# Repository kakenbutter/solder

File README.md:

# A 2-Bit Adder - *solder*
A poorly made PCB that is only slightly smarter than a goldfish. Ever wished to know the answer to life, the universe, and everything? Well this certainly can't tell you, but it can tell you what 3 + 3 is! Cool!

## Schematic

## PCB

## Features
- Won't explode/spontaneously combust*!
- Can add 2 numbers up to 3*!
- Turn on and off with potentiometer*!
- "Clean and neat" wiring on PCB*!

**probably*

## BOM
- 1 	Battery holder
- 6 	PNP Transistor
- 15	NPN Transistor
- 18  220k Resistor
- 1 	Potentiometer
- 4 	Push Button
- 4   LED

---

I do not assume any responsibility for any damage caused by using this PCB. 

Made by `@Ethan Zhou` as a part of https://solder.hackclub.com!

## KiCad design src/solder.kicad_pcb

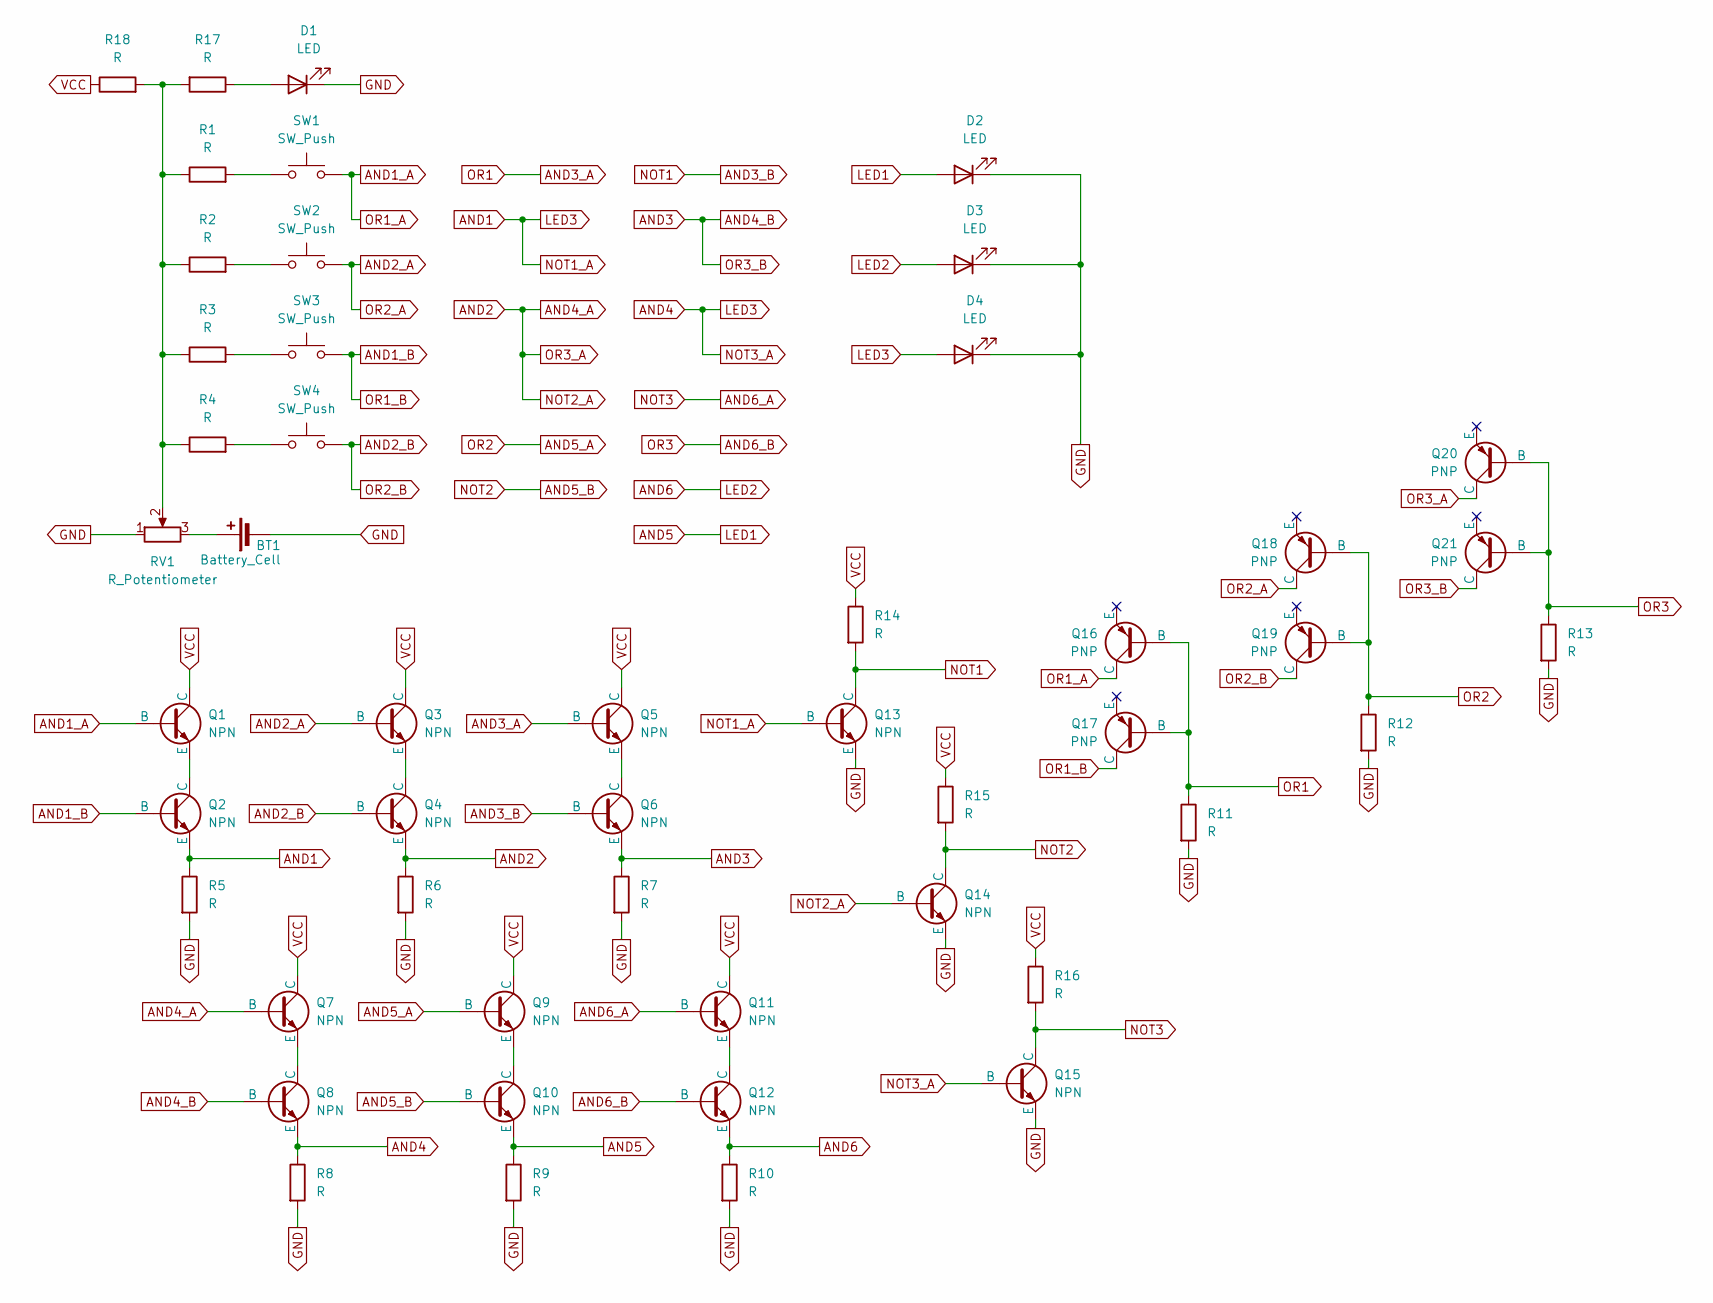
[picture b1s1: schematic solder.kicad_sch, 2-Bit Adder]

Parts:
BT1: Battery_Cell; BatteryHolder_Keystone_3034_1x20mm
D1, D2, D3, D4: LED; LED_D5.0mm
Q1, Q2, Q3, Q4, Q5, Q6, Q7, Q8, Q9, Q10, Q11, Q12, Q13, Q14, Q15: NPN; TO-92L_HandSolder
Q16, Q17, Q18, Q19, Q20, Q21: PNP; TO-92L_HandSolder
R1, R2, R3, R4, R5, R6, R7, R8, R9, R10, R11, R12, R13, R14, R15, R16, R17, R18: R; R_Axial_DIN0207_L6.3mm_D2.5mm_P7.62mm_Horizontal
RV1: R_Potentiometer; Potentiometer_Vishay_T73YP_Vertical
SW1, SW2, SW3, SW4: SW_Push; SW_PUSH_6mm

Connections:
AND1: D4.2 (A), Q2.3 (E), Q8.3 (E), Q13.2 (B), Q15.2 (B), R5.1, R8.1
AND1_A: Q1.2 (B), Q16.1 (C), SW1.2
AND1_B: Q2.2 (B), Q17.1 (C), SW3.2
AND2: Q4.3 (E), Q7.2 (B), Q14.2 (B), Q20.1 (C), R6.1
AND2_A: Q3.2 (B), Q18.1 (C), SW2.2
AND2_B: Q4.2 (B), Q19.1 (C), SW4.2
AND3: Q6.3 (E), Q8.2 (B), Q21.1 (C), R7.1
AND3_A: Q5.2 (B), Q16.2 (B), Q17.2 (B), R11.1
AND3_B: Q6.2 (B), Q13.1 (C), R14.2
AND5: D2.2 (A), Q10.3 (E), R9.1
AND5_A: Q9.2 (B), Q18.2 (B), Q19.2 (B), R12.1
AND5_B: Q10.2 (B), Q14.1 (C), R15.2
AND6: D3.2 (A), Q12.3 (E), R10.1
AND6_A: Q11.2 (B), Q15.1 (C), R16.2
AND6_B: Q12.2 (B), Q20.2 (B), Q21.2 (B), R13.1
GND: BT1.2 (-), D1.1 (K), D2.1 (K), D3.1 (K), D4.1 (K), Q13.3 (E), Q14.3 (E), Q15.3 (E), R5.2, R6.2, R7.2, R8.2, R9.2, R10.2, R11.2, R12.2, R13.2, RV1.1
unnamed: BT1.1 (+), RV1.3
unnamed: D1.2 (A), R17.1
unnamed: Q1.3 (E), Q2.1 (C)
unnamed: Q3.3 (E), Q4.1 (C)
unnamed: Q5.3 (E), Q6.1 (C)
unnamed: Q7.3 (E), Q8.1 (C)
unnamed: Q9.3 (E), Q10.1 (C)
unnamed: Q11.3 (E), Q12.1 (C)
unnamed: R1.1, R2.1, R3.1, R4.1, R17.2, R18.2, RV1.2
unnamed: R1.2, SW1.1
unnamed: R2.2, SW2.1
unnamed: R3.2, SW3.1
unnamed: R4.2, SW4.1
VCC: Q1.1 (C), Q3.1 (C), Q5.1 (C), Q7.1 (C), Q9.1 (C), Q11.1 (C), R14.1, R15.1, R16.1, R18.1

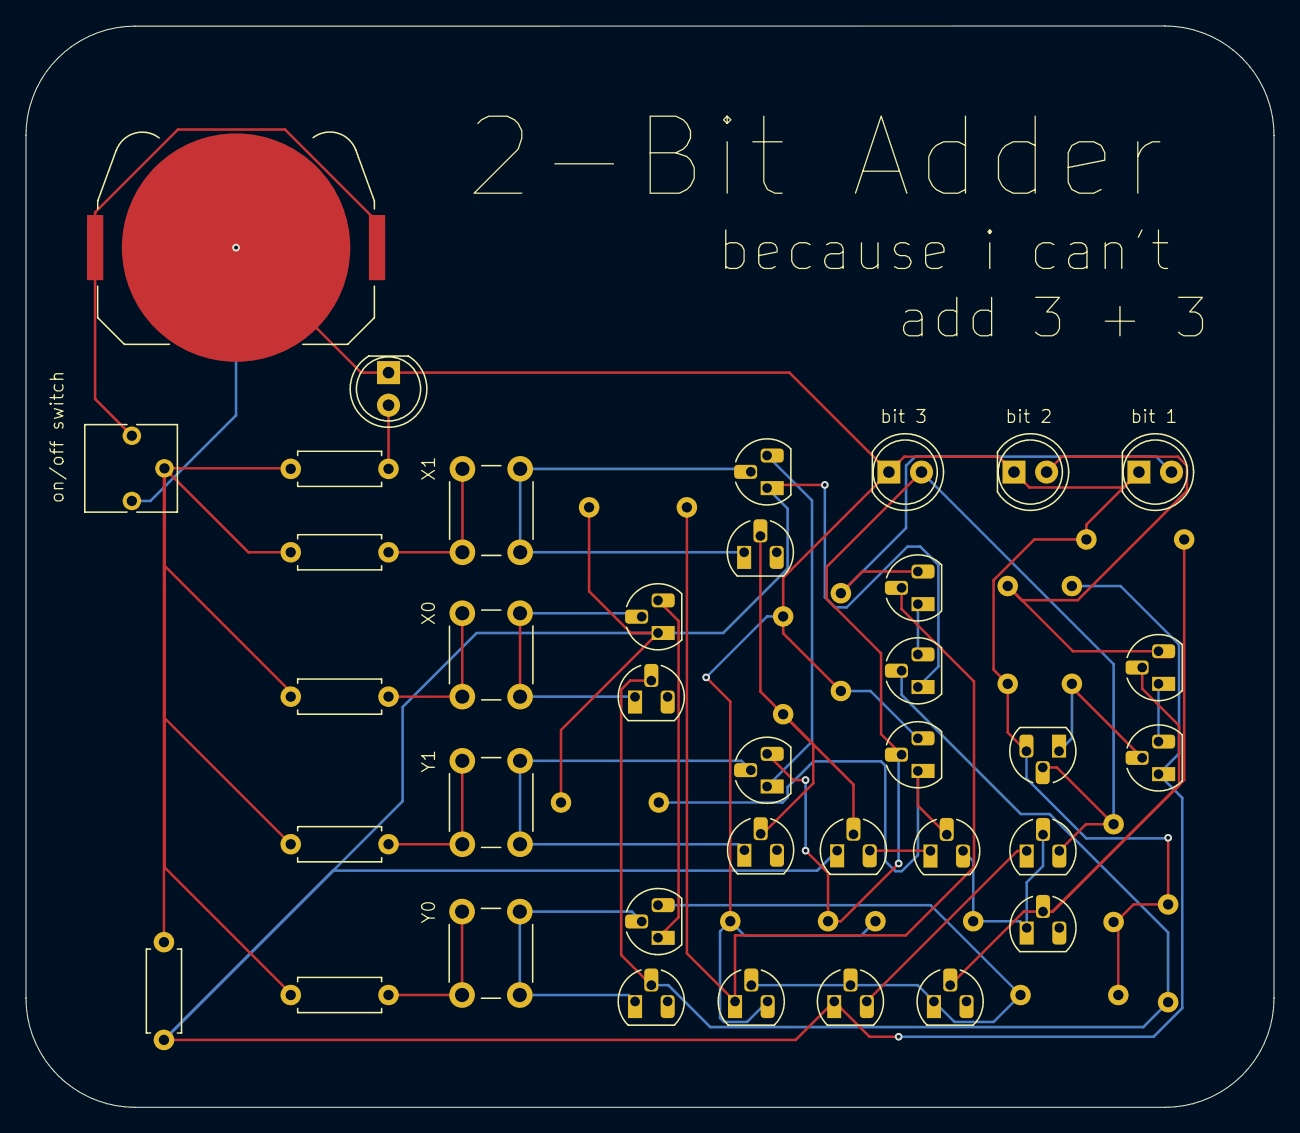
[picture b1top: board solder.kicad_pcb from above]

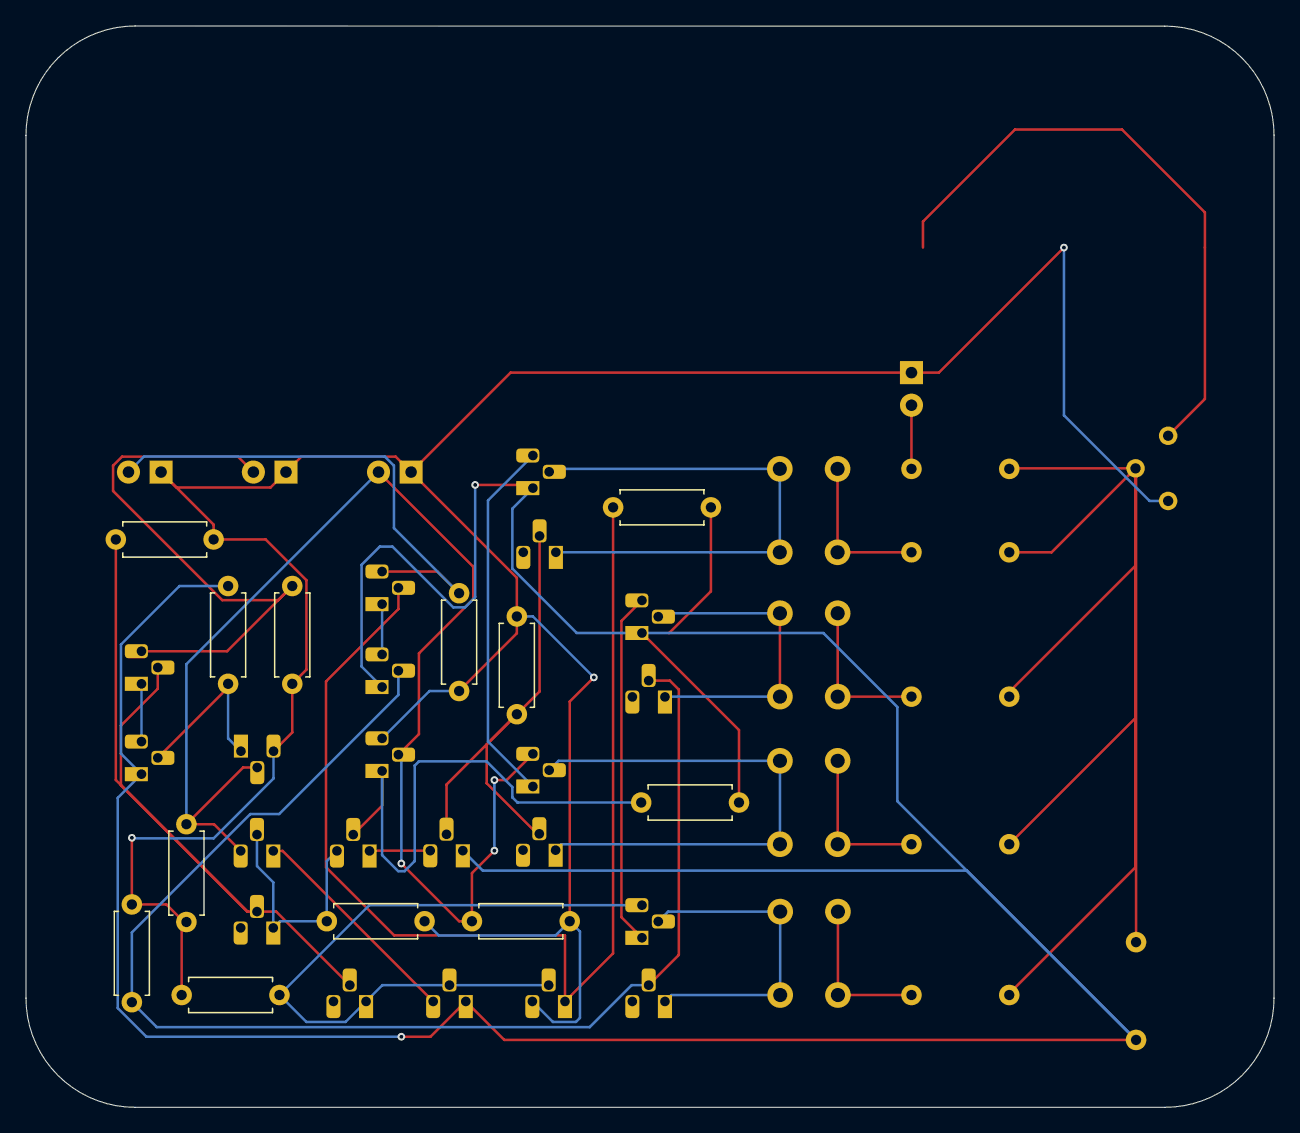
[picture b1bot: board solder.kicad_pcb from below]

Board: 2 copper layers, 97.2 x 84.3 mm, 49 parts (12 on the bottom side), 30 nets.

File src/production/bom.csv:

Designator,Footprint,Quantity,Value,LCSC Part #
BT1,BatteryHolder_Keystone_3034_1x20mm,1,Battery_Cell,
"D1, D2, D3, D4",LED_D5.0mm,4,LED,
"Q1, Q10, Q11, Q12, Q13, Q14, Q15, Q2, Q3, Q4, Q5, Q6, Q7, Q8, Q9",TO-92L_HandSolder,15,NPN,
"Q16, Q17, Q18, Q19, Q20, Q21",TO-92L_HandSolder,6,PNP,
"R1, R10, R11, R12, R13, R14, R15, R16, R17, R18, R2, R3, R4, R5, R6, R7, R8, R9",R_Axial_DIN0207_L6.3mm_D2.5mm_P7.62mm_Horizontal,18,R,
RV1,Potentiometer_Vishay_T73YP_Vertical,1,R_Potentiometer,
"SW1, SW2, SW3, SW4",SW_PUSH_6mm,4,SW_Push,

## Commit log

2025-05-20 Add images and update README.md
2025-05-20 Add src
